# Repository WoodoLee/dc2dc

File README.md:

# dc2dc
dc2dc converter development

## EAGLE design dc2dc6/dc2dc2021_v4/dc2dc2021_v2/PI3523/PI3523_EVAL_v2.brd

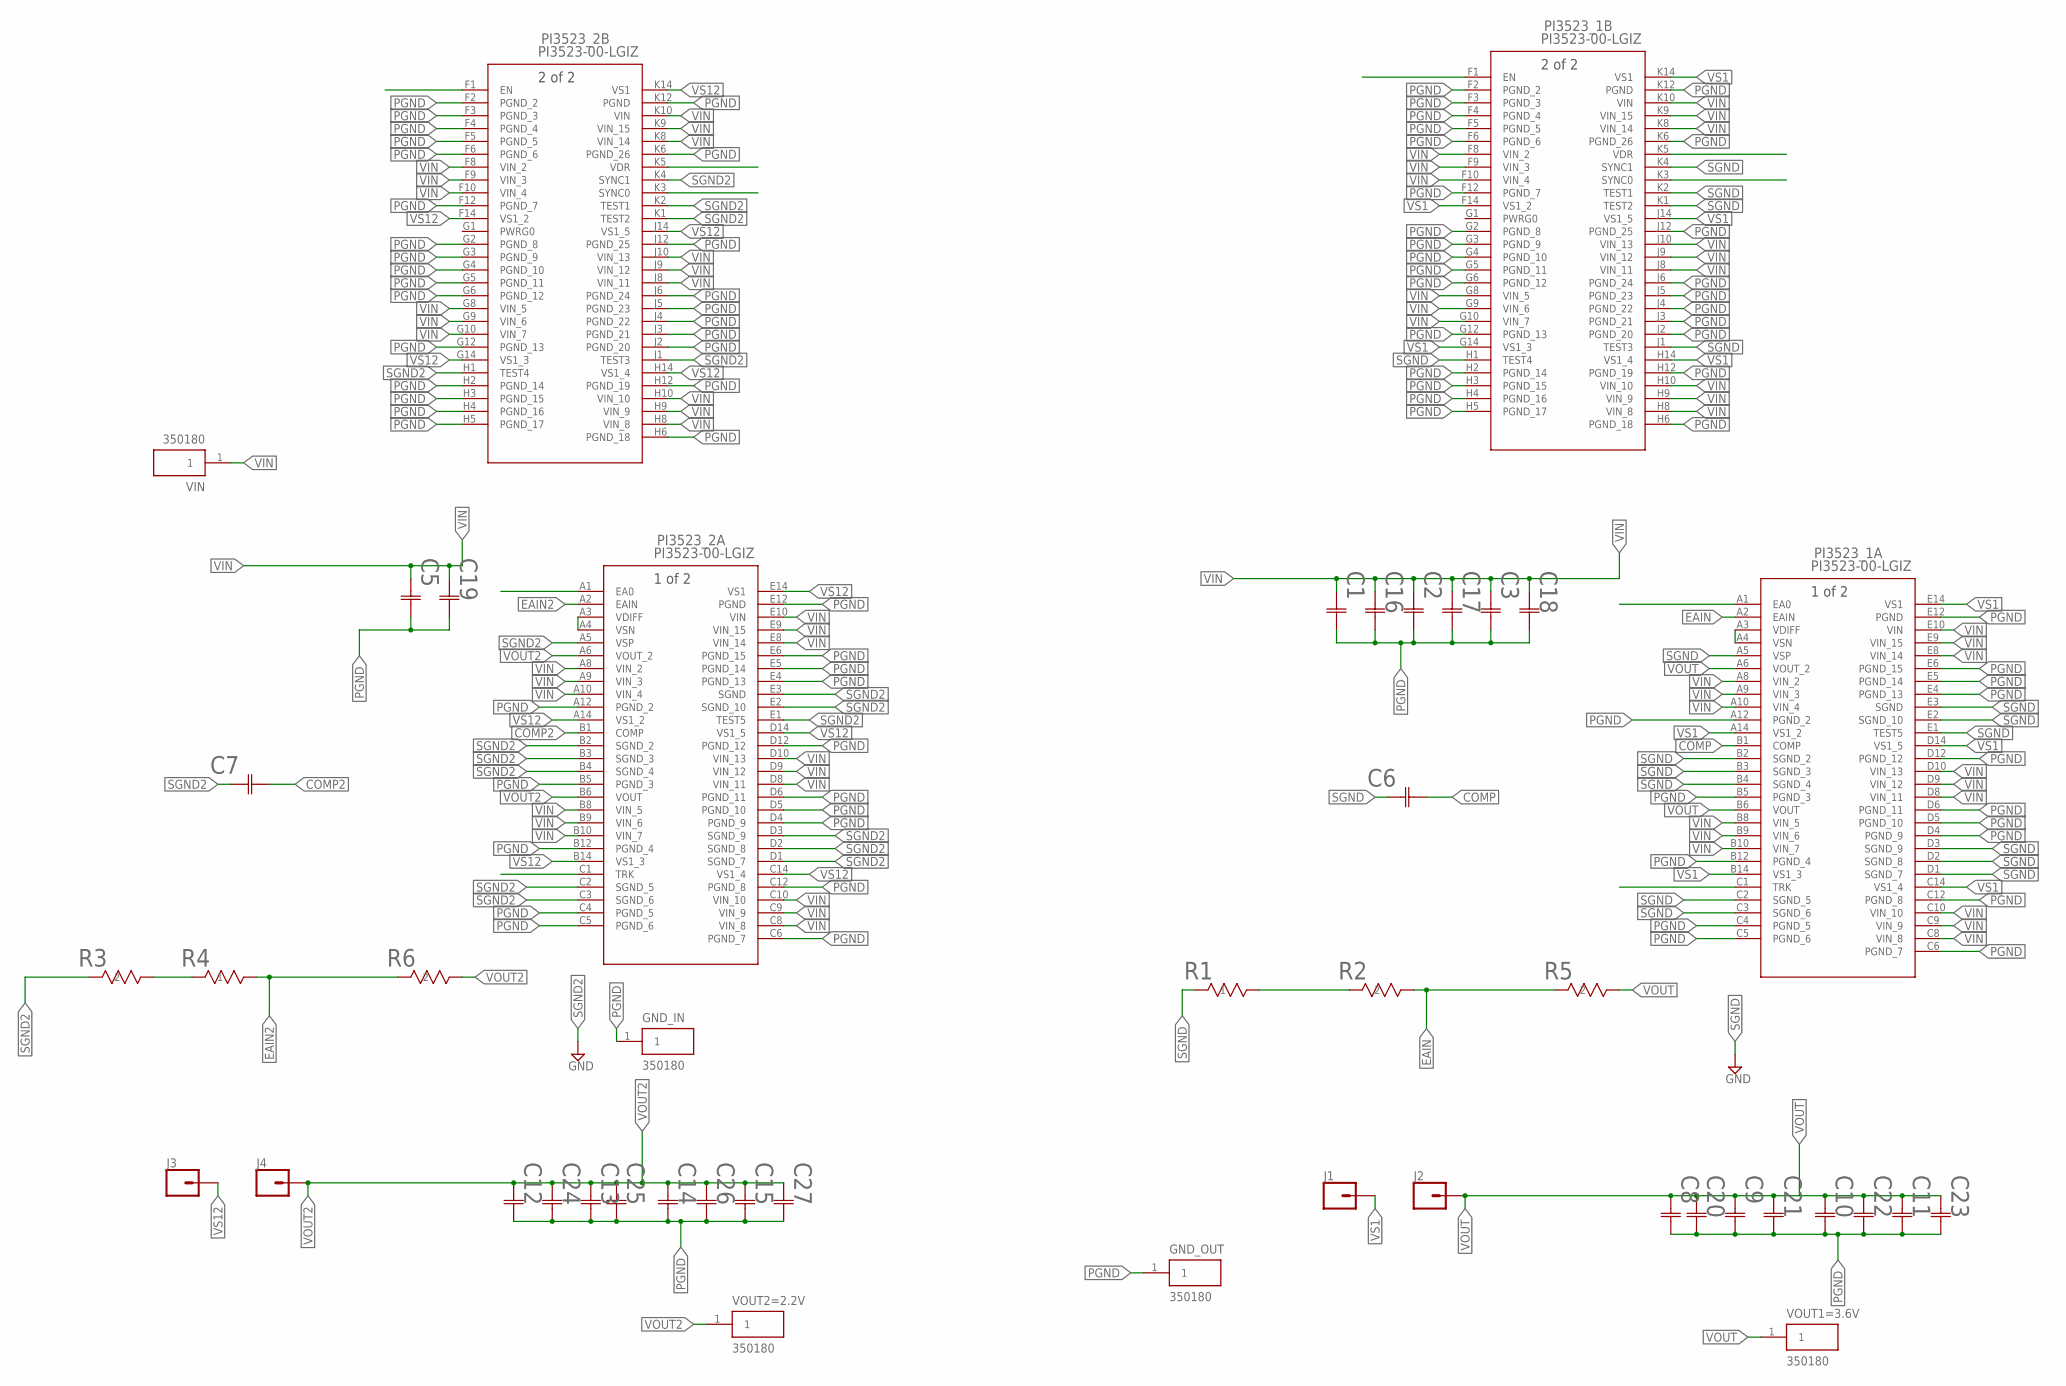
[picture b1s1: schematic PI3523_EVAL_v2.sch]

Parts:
C1, C2, C3, C5, C16, C17, C18, C19: GRM32ER72A225KA35L; G-32_MUR
C6, C7: C1608C0G2A472J080AC; CAP_C1608_TDK
C8, C9, C10, C11, C12, C13, C14, C15, C20, C21, C22, C23, C24, C25, C26, C27: GRM32EC80J107ME20L; G-32_MUR
GND_IN: 350180; TE_350180
GND_OUT: 350180; TE_350180
J1, J2, J3, J4: CONN_01; 1X01
PI3523_1, PI3523_2: PI3523-00-LGIZ; LGA_PI3523-00-LGIZ_VIC
R1: RL0816S-2R2-F; RES_0816_SUS
R2: RT0603BRD072K7L; RC0603N_YAG
R3: ERJ-3EKF12R4V; RC0603N_PAN
R4: ERA-3AEB1241V; RES_ERA3A_PAN
R5, R6: RT0603BRE072K4L; RC0603N_YAG
VIN: 350180; TE_350180
VOUT1=3.6V, VOUT2=2.2V: 350180; TE_350180

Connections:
COMP: C6.2, PI3523_1.B1 (COMP)
COMP2: C7.2, PI3523_2.B1 (COMP)
EAIN: PI3523_1.A2 (EAIN), R2.1, R5.2
EAIN2: PI3523_2.A2 (EAIN), R4.2, R6.2
unnamed: R3.1, R4.1
unnamed: PI3523_2.A3 (VDIFF), PI3523_2.A4 (VSN)
unnamed: PI3523_1.A3 (VDIFF), PI3523_1.A4 (VSN)
PGND: C1.2, C2.2, C3.2, C5.2, C8.2, C9.2, C10.2, C11.2, C12.2, C13.2, C14.2, C15.2, C16.2, C17.2, C18.2, C19.2, C20.2, C21.2, C22.2, C23.2, C24.2, C25.2, C26.2, C27.2, GND_IN.1, GND_OUT.1, PI3523_1.A12 (PGND_2), PI3523_1.B5 (PGND_3), PI3523_1.B12 (PGND_4), PI3523_1.C4 (PGND_5), PI3523_1.C5 (PGND_6), PI3523_1.C6 (PGND_7), PI3523_1.C12 (PGND_8), PI3523_1.D4 (PGND_9), PI3523_1.D5 (PGND_10), PI3523_1.D6 (PGND_11), PI3523_1.D12 (PGND_12), PI3523_1.E4 (PGND_13), PI3523_1.E5 (PGND_14), PI3523_1.E6 (PGND_15), PI3523_1.E12 (PGND), PI3523_1.F2 (PGND_2), PI3523_1.F3 (PGND_3), PI3523_1.F4 (PGND_4), PI3523_1.F5 (PGND_5), PI3523_1.F6 (PGND_6), PI3523_1.F12 (PGND_7), PI3523_1.G2 (PGND_8), PI3523_1.G3 (PGND_9), PI3523_1.G4 (PGND_10), PI3523_1.G5 (PGND_11), PI3523_1.G6 (PGND_12), PI3523_1.G12 (PGND_13), PI3523_1.H2 (PGND_14), PI3523_1.H3 (PGND_15), PI3523_1.H4 (PGND_16), PI3523_1.H5 (PGND_17), PI3523_1.H6 (PGND_18), PI3523_1.H12 (PGND_19), PI3523_1.J2 (PGND_20), PI3523_1.J3 (PGND_21), PI3523_1.J4 (PGND_22), PI3523_1.J5 (PGND_23), PI3523_1.J6 (PGND_24), PI3523_1.J12 (PGND_25), PI3523_1.K6 (PGND_26), PI3523_1.K12 (PGND), PI3523_2.A12 (PGND_2), PI3523_2.B5 (PGND_3), PI3523_2.B12 (PGND_4), PI3523_2.C4 (PGND_5), PI3523_2.C5 (PGND_6), PI3523_2.C6 (PGND_7), PI3523_2.C12 (PGND_8), PI3523_2.D4 (PGND_9), PI3523_2.D5 (PGND_10), PI3523_2.D6 (PGND_11), PI3523_2.D12 (PGND_12), PI3523_2.E4 (PGND_13), PI3523_2.E5 (PGND_14), PI3523_2.E6 (PGND_15), PI3523_2.E12 (PGND), PI3523_2.F2 (PGND_2), PI3523_2.F3 (PGND_3), PI3523_2.F4 (PGND_4), PI3523_2.F5 (PGND_5), PI3523_2.F6 (PGND_6), PI3523_2.F12 (PGND_7), PI3523_2.G2 (PGND_8), PI3523_2.G3 (PGND_9), PI3523_2.G4 (PGND_10), PI3523_2.G5 (PGND_11), PI3523_2.G6 (PGND_12), PI3523_2.G12 (PGND_13), PI3523_2.H2 (PGND_14), PI3523_2.H3 (PGND_15), PI3523_2.H4 (PGND_16), PI3523_2.H5 (PGND_17), PI3523_2.H6 (PGND_18), PI3523_2.H12 (PGND_19), PI3523_2.J2 (PGND_20), PI3523_2.J3 (PGND_21), PI3523_2.J4 (PGND_22), PI3523_2.J5 (PGND_23), PI3523_2.J6 (PGND_24), PI3523_2.J12 (PGND_25), PI3523_2.K6 (PGND_26), PI3523_2.K12 (PGND)
R21_1: R1.2, R2.2
SGND: C6.1, PI3523_1.A5 (VSP), PI3523_1.B2 (SGND_2), PI3523_1.B3 (SGND_3), PI3523_1.B4 (SGND_4), PI3523_1.C2 (SGND_5), PI3523_1.C3 (SGND_6), PI3523_1.D1 (SGND_7), PI3523_1.D2 (SGND_8), PI3523_1.D3 (SGND_9), PI3523_1.E1 (TEST5), PI3523_1.E2 (SGND_10), PI3523_1.E3 (SGND), PI3523_1.H1 (TEST4), PI3523_1.J1 (TEST3), PI3523_1.K1 (TEST2), PI3523_1.K2 (TEST1), PI3523_1.K4 (SYNC1), R1.1
SGND2: C7.1, PI3523_2.A5 (VSP), PI3523_2.B2 (SGND_2), PI3523_2.B3 (SGND_3), PI3523_2.B4 (SGND_4), PI3523_2.C2 (SGND_5), PI3523_2.C3 (SGND_6), PI3523_2.D1 (SGND_7), PI3523_2.D2 (SGND_8), PI3523_2.D3 (SGND_9), PI3523_2.E1 (TEST5), PI3523_2.E2 (SGND_10), PI3523_2.E3 (SGND), PI3523_2.H1 (TEST4), PI3523_2.J1 (TEST3), PI3523_2.K1 (TEST2), PI3523_2.K2 (TEST1), PI3523_2.K4 (SYNC1), R3.2
VIN: C1.1, C2.1, C3.1, C5.1, C16.1, C17.1, C18.1, C19.1, PI3523_1.A8 (VIN_2), PI3523_1.A9 (VIN_3), PI3523_1.A10 (VIN_4), PI3523_1.B8 (VIN_5), PI3523_1.B9 (VIN_6), PI3523_1.B10 (VIN_7), PI3523_1.C8 (VIN_8), PI3523_1.C9 (VIN_9), PI3523_1.C10 (VIN_10), PI3523_1.D8 (VIN_11), PI3523_1.D9 (VIN_12), PI3523_1.D10 (VIN_13), PI3523_1.E8 (VIN_14), PI3523_1.E9 (VIN_15), PI3523_1.E10 (VIN), PI3523_1.F8 (VIN_2), PI3523_1.F9 (VIN_3), PI3523_1.F10 (VIN_4), PI3523_1.G8 (VIN_5), PI3523_1.G9 (VIN_6), PI3523_1.G10 (VIN_7), PI3523_1.H8 (VIN_8), PI3523_1.H9 (VIN_9), PI3523_1.H10 (VIN_10), PI3523_1.J8 (VIN_11), PI3523_1.J9 (VIN_12), PI3523_1.J10 (VIN_13), PI3523_1.K8 (VIN_14), PI3523_1.K9 (VIN_15), PI3523_1.K10 (VIN), PI3523_2.A8 (VIN_2), PI3523_2.A9 (VIN_3), PI3523_2.A10 (VIN_4), PI3523_2.B8 (VIN_5), PI3523_2.B9 (VIN_6), PI3523_2.B10 (VIN_7), PI3523_2.C8 (VIN_8), PI3523_2.C9 (VIN_9), PI3523_2.C10 (VIN_10), PI3523_2.D8 (VIN_11), PI3523_2.D9 (VIN_12), PI3523_2.D10 (VIN_13), PI3523_2.E8 (VIN_14), PI3523_2.E9 (VIN_15), PI3523_2.E10 (VIN), PI3523_2.F8 (VIN_2), PI3523_2.F9 (VIN_3), PI3523_2.F10 (VIN_4), PI3523_2.G8 (VIN_5), PI3523_2.G9 (VIN_6), PI3523_2.G10 (VIN_7), PI3523_2.H8 (VIN_8), PI3523_2.H9 (VIN_9), PI3523_2.H10 (VIN_10), PI3523_2.J8 (VIN_11), PI3523_2.J9 (VIN_12), PI3523_2.J10 (VIN_13), PI3523_2.K8 (VIN_14), PI3523_2.K9 (VIN_15), PI3523_2.K10 (VIN), VIN.1
VOUT: C8.1, C9.1, C10.1, C11.1, C20.1, C21.1, C22.1, C23.1, J2.1, PI3523_1.A6 (VOUT_2), PI3523_1.B6 (VOUT), R5.1, VOUT1=3.6V.1
VOUT2: C12.1, C13.1, C14.1, C15.1, C24.1, C25.1, C26.1, C27.1, J4.1, PI3523_2.A6 (VOUT_2), PI3523_2.B6 (VOUT), R6.1, VOUT2=2.2V.1
VS1: J1.1, PI3523_1.A14 (VS1_2), PI3523_1.B14 (VS1_3), PI3523_1.C14 (VS1_4), PI3523_1.D14 (VS1_5), PI3523_1.E14 (VS1), PI3523_1.F14 (VS1_2), PI3523_1.G14 (VS1_3), PI3523_1.H14 (VS1_4), PI3523_1.J14 (VS1_5), PI3523_1.K14 (VS1)
VS12: J3.1, PI3523_2.A14 (VS1_2), PI3523_2.B14 (VS1_3), PI3523_2.C14 (VS1_4), PI3523_2.D14 (VS1_5), PI3523_2.E14 (VS1), PI3523_2.F14 (VS1_2), PI3523_2.G14 (VS1_3), PI3523_2.H14 (VS1_4), PI3523_2.J14 (VS1_5), PI3523_2.K14 (VS1)

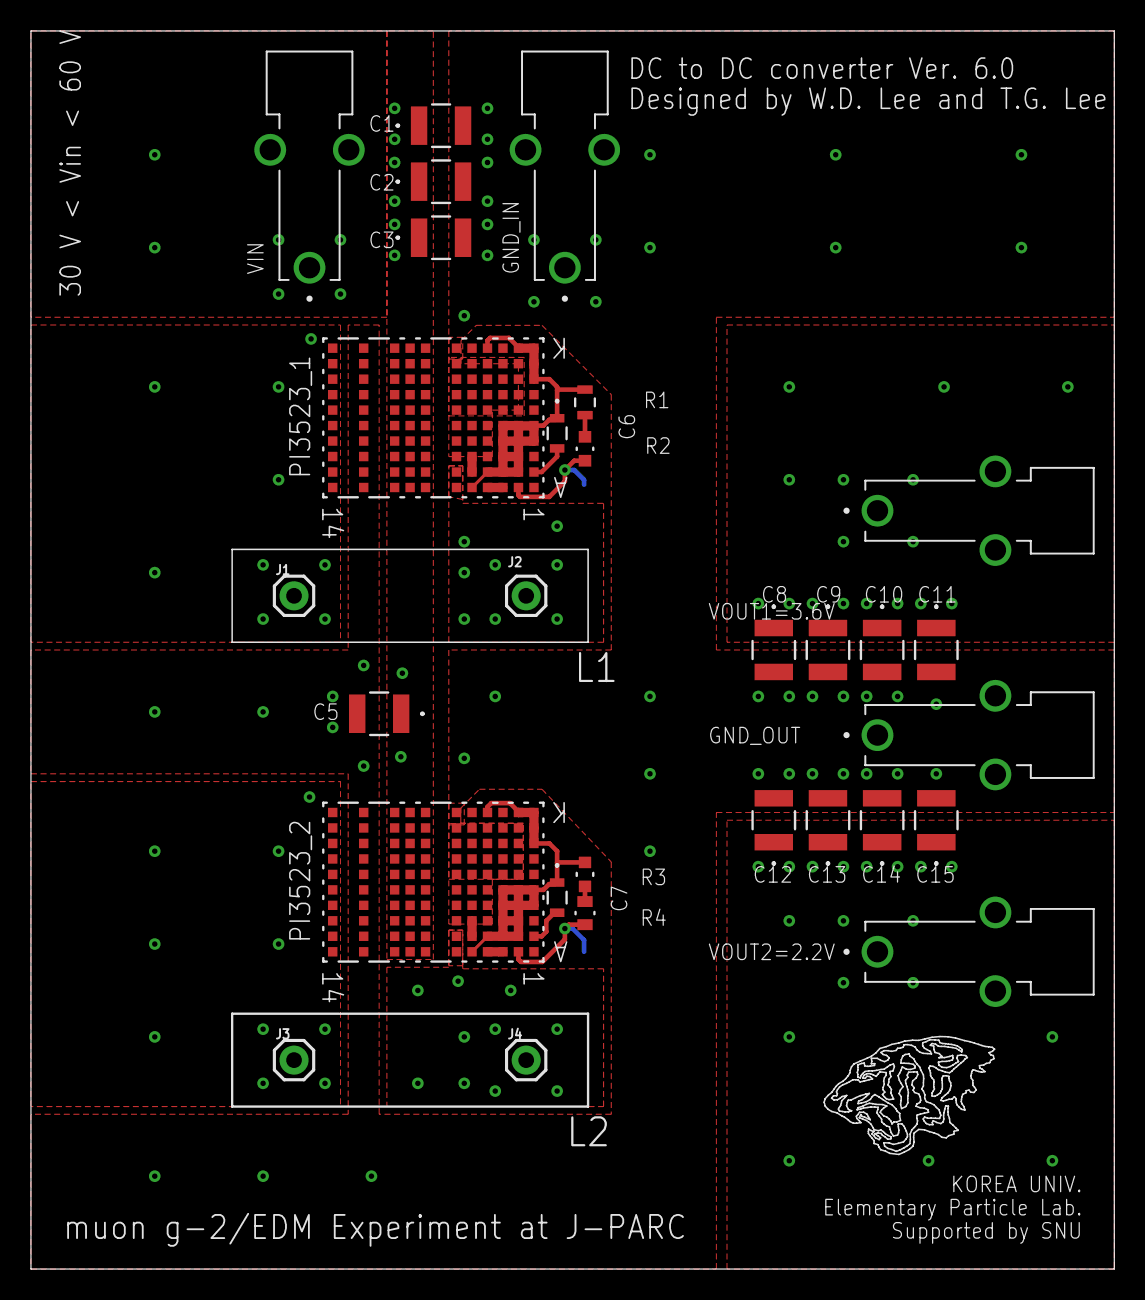
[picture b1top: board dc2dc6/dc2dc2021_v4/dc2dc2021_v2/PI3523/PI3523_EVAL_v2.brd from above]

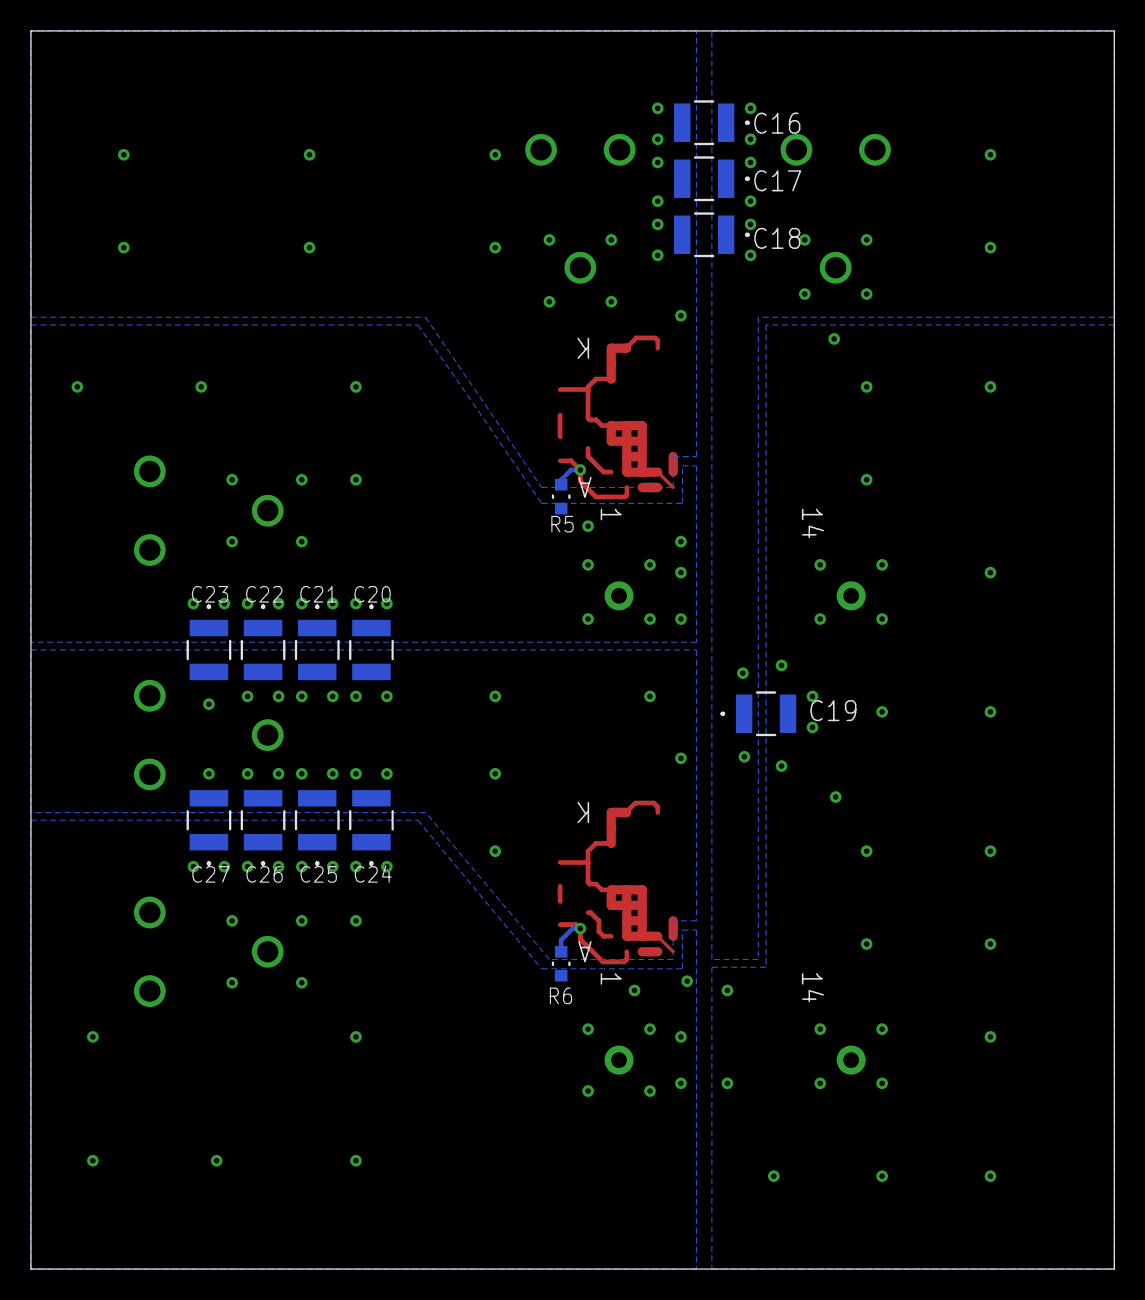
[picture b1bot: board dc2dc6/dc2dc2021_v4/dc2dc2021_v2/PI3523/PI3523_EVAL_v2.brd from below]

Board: 4 copper layers, 70.0 x 80.0 mm, 43 parts (14 on the bottom side), 16 nets.

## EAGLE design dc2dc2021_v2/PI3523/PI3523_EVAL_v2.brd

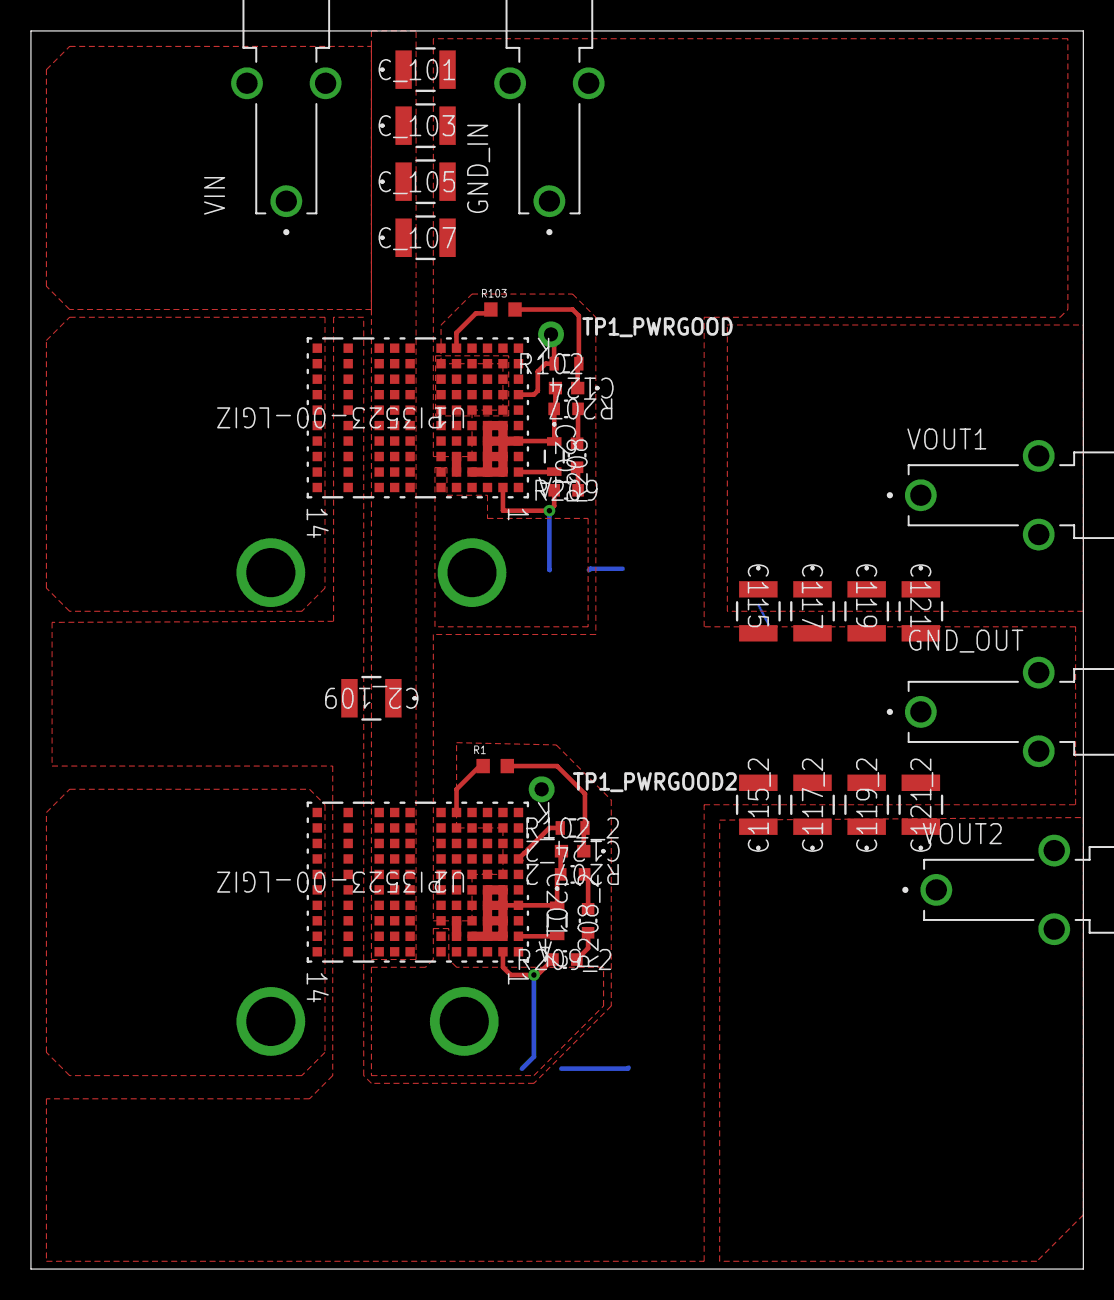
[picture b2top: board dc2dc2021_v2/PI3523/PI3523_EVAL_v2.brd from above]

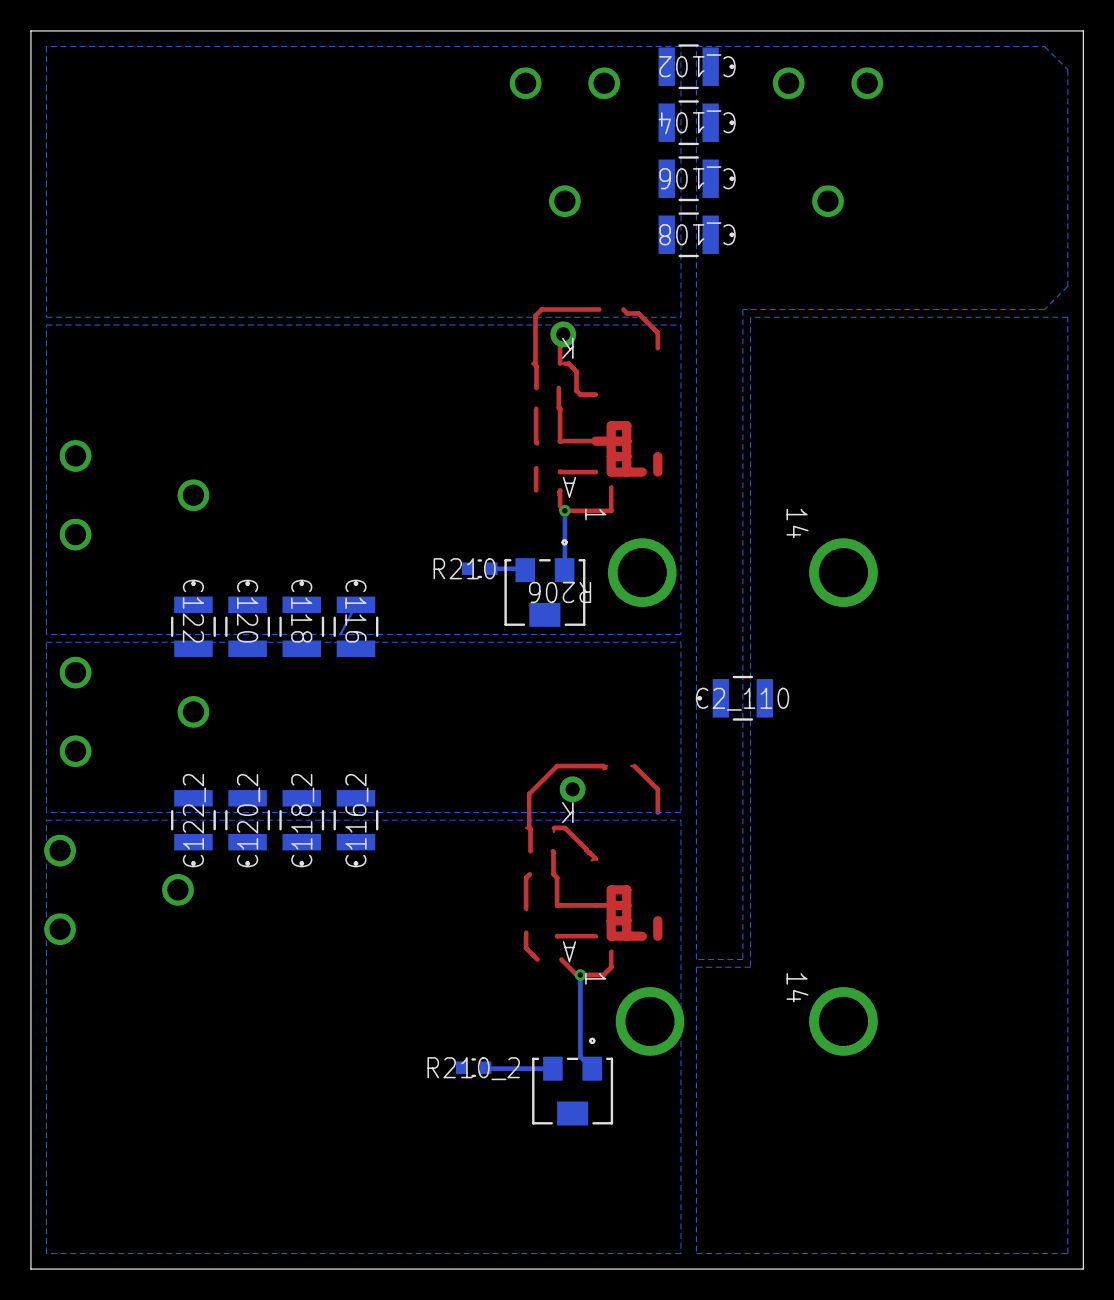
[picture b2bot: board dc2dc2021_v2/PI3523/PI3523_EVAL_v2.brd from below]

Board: 4 copper layers, 68.0 x 80.0 mm, 57 parts (17 on the bottom side), 24 nets.

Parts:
C2_109, C2_110: GRM32ER72A225KA35L; G-32_MUR
C115, C115_2, C116, C116_2, C117, C117_2, C118, C118_2, C119, C119_2, C120, C120_2, C121, C121_2, C122, C122_2: GRM32ER72A225KA35K; G-32_MUR
C124, C124_2: GRM188R72A104KA35J; G-188_MUR
C201, C201_2: C1608C0G2A472J080AC; CAP_C1608_TDK
C_101, C_102, C_103, C_104, C_105, C_106, C_107, C_108: GRM32ER72A225KA35L; G-32_MUR
GND_IN: 350180; TE_350180
GND_OUT: 350180; TE_350180
MGT1, MGT2, MGT3, MGT4: MOUNTING_HOLE; BEAGLEBONEBLACK_MOUNTING_HOLE
R1, R103: RK73H1JTTD1001F; RESC1608X55N
R102, R102_2: RK73H1JTTD1002F; RES_TTD1002F_KOA
R206, R206_2: 3224W-1-502E; POT_3224W
R207, R207_2: RC0603FR-077R5L; RC0603N_YAG
R208, R208_2: RT0603BRD071KL; RC0603N_YAG
R209, R209_2: RT0603BRD071K37L; RC0603N_YAG
R210, R210_2: RT0603BRE072K4L; RC0603N_YAG
TP1_PWRGOOD, TP1_PWRGOOD2: TESTPOINT_TPS-PAD-036; TESTPOINT_PAD-036
U1, U2: PI3523-00-LGIZ; LGA_PI3523-00-LGIZ_VIC
VIN: 350180; TE_350180
VOUT1, VOUT2: 350180; TE_350180

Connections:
COMP: C201.2, U1.B1
COMP2: C201_2.2, U2.B1
EAIN: R206.1, R209.1, U1.A2
EAIN2: R206_2.1, R209_2.1, U2.A2
unnamed: R207.1, R208.2
unnamed: R208.1, R209.2
unnamed: R206.3, R210.2
unnamed: R207_2.1, R208_2.2
unnamed: R208_2.1, R209_2.2
unnamed: R206_2.3, R210_2.2
unnamed: C124_2.1, R1.2, R102_2.2
unnamed: C124.1, R102.2, R103.2
PGND: C2_109.2, C2_110.2, C115.2, C115_2.2, C116.2, C116_2.2, C117.2, C117_2.2, C118.2, C118_2.2, C119.2, C119_2.2, C120.2, C120_2.2, C121.2, C121_2.2, C122.2, C122_2.2, C_101.2, C_102.2, C_103.2, C_104.2, C_105.2, C_106.2, C_107.2, C_108.2, GND_IN.1, GND_OUT.1, U1.A12, U1.B5, U1.B12, U1.C4, U1.C5, U1.C6, U1.C12, U1.D4, U1.D5, U1.D6, U1.D12, U1.E4, U1.E5, U1.E6, U1.E12, U1.F2, U1.F3, U1.F4, U1.F5, U1.F6, U1.F12, U1.G2, U1.G3, U1.G4, U1.G5, U1.G6, U1.G12, U1.H2, U1.H3, U1.H4, U1.H5, U1.H6, U1.H12, U1.J2, U1.J3, U1.J4, U1.J5, U1.J6, U1.J12, U1.K6, U1.K12, U2.A12, U2.B5, U2.B12, U2.C4, U2.C5, U2.C6, U2.C12, U2.D4, U2.D5, U2.D6, U2.D12, U2.E4, U2.E5, U2.E6, U2.E12, U2.F2, U2.F3, U2.F4, U2.F5, U2.F6, U2.F12, U2.G2, U2.G3, U2.G4, U2.G5, U2.G6, U2.G12, U2.H2, U2.H3, U2.H4, U2.H5, U2.H6, U2.H12, U2.J2, U2.J3, U2.J4, U2.J5, U2.J6, U2.J12, U2.K6, U2.K12
PWRGOOD: R102.1, TP1_PWRGOOD.1, U1.G1
PWRGOOD2: R102_2.1, TP1_PWRGOOD2.1, U2.G1
SGND: C124.2, C201.1, R207.2, U1.B2, U1.B3, U1.B4, U1.C2, U1.C3, U1.D1, U1.D2, U1.D3, U1.E2, U1.E3
SGND2: C124_2.2, C201_2.1, R207_2.2, U2.B2, U2.B3, U2.B4, U2.C2, U2.C3, U2.D1, U2.D2, U2.D3, U2.E2, U2.E3
VDR: R103.1, U1.K5
VDR2: R1.1, U2.K5
VIN: C2_109.1, C2_110.1, C_101.1, C_102.1, C_103.1, C_104.1, C_105.1, C_106.1, C_107.1, C_108.1, U1.A8, U1.A9, U1.A10, U1.B8, U1.B9, U1.B10, U1.C8, U1.C9, U1.C10, U1.D8, U1.D9, U1.D10, U1.E8, U1.E9, U1.E10, U1.F8, U1.F9, U1.F10, U1.G8, U1.G9, U1.G10, U1.H8, U1.H9, U1.H10, U1.J8, U1.J9, U1.J10, U1.K8, U1.K9, U1.K10, U2.A8, U2.A9, U2.A10, U2.B8, U2.B9, U2.B10, U2.C8, U2.C9, U2.C10, U2.D8, U2.D9, U2.D10, U2.E8, U2.E9, U2.E10, U2.F8, U2.F9, U2.F10, U2.G8, U2.G9, U2.G10, U2.H8, U2.H9, U2.H10, U2.J8, U2.J9, U2.J10, U2.K8, U2.K9, U2.K10, VIN.1
VOUT: C115.1, C116.1, C117.1, C118.1, C119.1, C120.1, C121.1, C122.1, MGT2.P$1, R210.1, U1.A6, U1.B6, VOUT1.1
VOUT2: C115_2.1, C116_2.1, C117_2.1, C118_2.1, C119_2.1, C120_2.1, C121_2.1, C122_2.1, MGT4.P$1, R210_2.1, U2.A6, U2.B6, VOUT2.1
VS1: MGT1.P$1, U1.A14, U1.B14, U1.C14, U1.D14, U1.E14, U1.F14, U1.G14, U1.H14, U1.J14, U1.K14
VS12: MGT3.P$1, U2.A14, U2.B14, U2.C14, U2.D14, U2.E14, U2.F14, U2.G14, U2.H14, U2.J14, U2.K14

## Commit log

2020-07-29 coil
2021-03-24 dc2dc
2021-04-01 dc2dc6

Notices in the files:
parts and their libraries:
COPYRIGHT: Copyright (C) 2015 Accelerated Designs. All rights reserved
COPYRIGHT: Copyright (C) 2018 Accelerated Designs. All rights reserved
SparkFun-Connectors: Licensing: Creative Commons ShareAlike 4.0 International - https://creativecommons.org/licenses/by-sa/4.0
